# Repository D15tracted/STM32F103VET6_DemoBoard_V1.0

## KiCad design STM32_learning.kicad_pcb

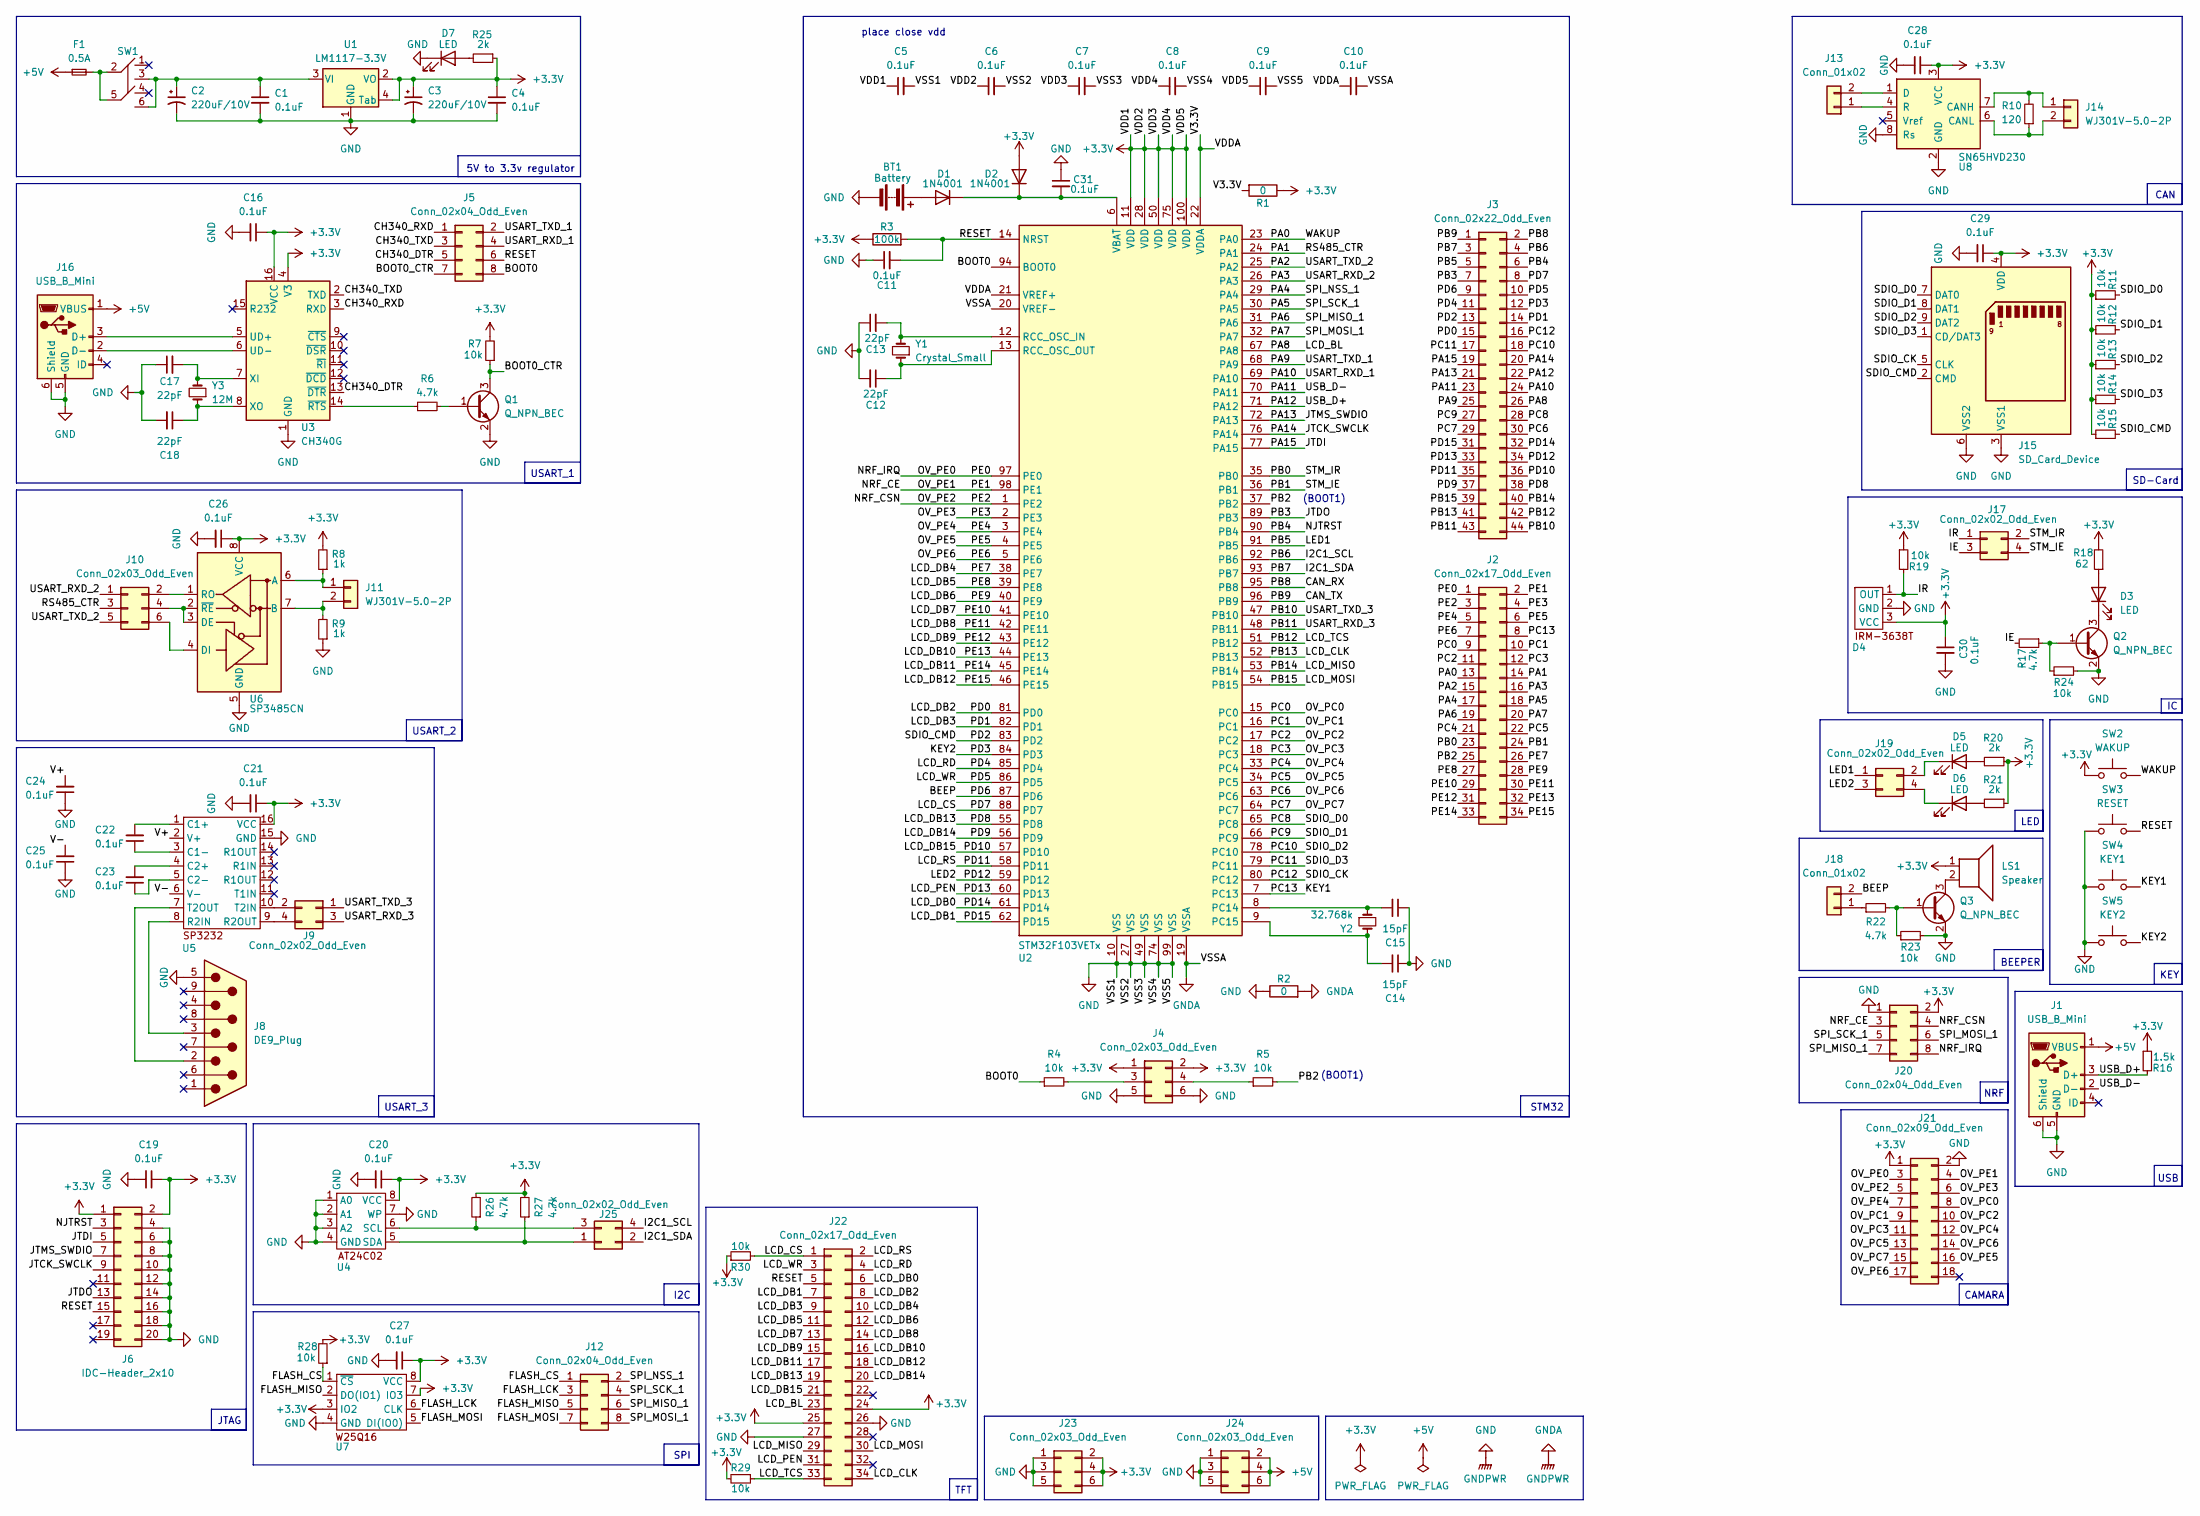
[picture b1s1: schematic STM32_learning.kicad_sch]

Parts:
BT1: Battery; CR1220-2
C1, C4, C5, C6, C7, C8, C9, C10, C11, C16, C19, C20, C21, C22, C23, C24, C25, C26, C27, C28, C29, C30, C31: 0.1uF; C_0603_1608Metric
C2, C3: 220uF/10V; C_Elec_6.3x5.4
C12, C13, C17, C18: 22pF; C_0603_1608Metric
C14, C15: 15pF; C_0603_1608Metric
D1, D2: 1N4001; D_MiniMELF
D3: LED; LED_D5.0mm_Horizontal_O3.81mm_Z15.0mm
D4: IRM-3638T
D5, D6, D7: LED; LED_0805_2012Metric
F1: 0.5A; Fuse_0805_2012Metric
J1, J16: USB_B_Mini; USB_Mini-B_Wuerth_65100516121_Horizontal
J2: Conn_02x17_Odd_Even; Conn2x17P
J3: Conn_02x22_Odd_Even; Conn2x22P
J4, J10, J23, J24: Conn_02x03_Odd_Even; Conn2x03P
J5, J12, J20: Conn_02x04_Odd_Even; Conn2x04P
J6: IDC-Header_2x10; IDC-Header_2x10_P2.54mm_Vertical
J8: DE9_Plug; DSUB-9_Female_Horizontal_P2.77x2.84mm_EdgePinOffset4.94mm_H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
J9, J17, J19, J25: Conn_02x02_Odd_Even; Conn2x02P
J11, J14: WJ301V-5.0-2P
J13, J18: Conn_01x02; Conn1x02P
J15: SD_Card_Device; SD-102
J21: Conn_02x09_Odd_Even; Conn2x09P
J22: Conn_02x17_Odd_Even; SKUMRB2801
LS1: Speaker; Beeper9mm
Q1, Q2, Q3: Q_NPN_BEC; SOT-23
R1, R2: 0; R_0603_1608Metric
R3: 100k; R_0603_1608Metric
R4, R5, R7, R11, R12, R13, R14, R15, R19, R23, R24, R28, R29, R30: 10k; R_0603_1608Metric
R6, R17, R22, R26, R27: 4.7k; R_0603_1608Metric
R8, R9: 1k; R_0603_1608Metric
R10: 120; R_0603_1608Metric
R16: 1.5k; R_0603_1608Metric
R18: 62; R_0805_2012Metric
R20, R21, R25: 2k; R_0603_1608Metric
SW1: TK-6580-1
SW2: WAKUP; KEY6x6
SW3: RESET; KEY6x6
SW4: KEY1; KEY6x6
SW5: KEY2; KEY6x6
U1: LM1117-3.3V; SOT-223
U2: STM32F103VETx; LQFP-100_14x14mm_P0.5mm
U3: CH340G; SOIC-16_3.9x9.9mm_P1.27mm
U4, U7: SOIC-8
U5: SOIC-16
U6: SP3485CN; SOIC-8_3.9x4.9mm_P1.27mm
U8: SN65HVD230; SOIC-8_3.9x4.9mm_P1.27mm
Y1: Crystal_Small; Crystal_HC49-U_Vertical
Y2: 32.768k; SMD-3215-2P
Y3: 12M; Crystal_HC49-U_Vertical

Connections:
+3.3V: C3.1, C4.1, C5.1, C6.1, C7.1, C8.1, C9.1, C16.1, C19.1, C20.1, C21.1, C26.1, C27.1, C28.1, C29.1, C30.1, D2.2 (A), D4.3 (VCC), J4.1, J4.2, J6.1, J6.2, J15.4 (VDD), J20.2, J21.1, J22.24, J22.25, J23.2, J23.4, J23.6, LS1.1, R1.1, R3.1, R7.2, R8.2, R11.1, R12.1, R13.1, R14.1, R15.1, R16.1, R18.2, R19.1, R20.1, R21.1, R25.1, R26.2, R27.2, R28.2, R29.2, R30.1, SW2.1, U1.2 (VO), U1.4 (Tab), U2.11 (VDD), U2.28 (VDD), U2.50 (VDD), U2.75 (VDD), U2.100 (VDD), U3.4 (V3), U3.16 (VCC), U4.8 (VCC), U5.16 (VCC), U6.8 (VCC), U7.3 (IO2), U7.7 (IO3), U7.8 (VCC), U8.3 (VCC)
/BEEP: J3.9, J18.2, U2.87 (PD6)
/BOOT0: J5.8, R4.1, U2.94 (BOOT0)
/BOOT0_CTR: J5.7, Q1.3 (C), R7.1
/CAN_RX: J3.2, U2.95 (PB8)
/CAN_TX: J3.1, U2.96 (PB9)
/CH340_DTR: J5.5, U3.13 (~DTR)
/CH340_RXD: J5.1, U3.3 (RXD)
/CH340_TXD: J5.3, U3.2 (TXD)
/FLASH_CS: J12.1, R28.1, U7.1 (~CS)
/FLASH_LCK: J12.3, U7.6 (CLK)
/FLASH_MISO: J12.5, U7.2 (DO(IO1))
/FLASH_MOSI: J12.7, U7.5 (DI(IO0))
/I2C1_SCL: J3.4, J25.4, U2.92 (PB6)
/I2C1_SDA: J3.3, J25.2, U2.93 (PB7)
/IE: J17.3, R17.2
/IR: D4.1 (OUT), J17.1, R19.2
/JTCK_SWCLK: J3.20, J6.9, U2.76 (PA14)
/JTDI: J3.19, J6.5, U2.77 (PA15)
/JTDO: J3.7, J6.13, U2.89 (PB3)
/JTMS_SWDIO: J3.21, J6.7, U2.72 (PA13)
/KEY1: J2.8, SW4.2, U2.7 (PC13)
/KEY2: J3.12, SW5.2, U2.84 (PD3)
/LCD_BL: J3.26, J22.23, U2.67 (PA8)
/LCD_CLK: J3.41, J22.34, U2.52 (PB13)
/LCD_CS: J3.8, J22.1, R30.2, U2.88 (PD7)
/LCD_DB0: J3.32, J22.6, U2.61 (PD14)
/LCD_DB1: J3.31, J22.7, U2.62 (PD15)
/LCD_DB2: J3.15, J22.8, U2.81 (PD0)
/LCD_DB3: J3.14, J22.9, U2.82 (PD1)
/LCD_DB4: J2.26, J22.10, U2.38 (PE7)
/LCD_DB5: J2.27, J22.11, U2.39 (PE8)
/LCD_DB6: J2.28, J22.12, U2.40 (PE9)
/LCD_DB7: J2.29, J22.13, U2.41 (PE10)
/LCD_DB8: J2.30, J22.14, U2.42 (PE11)
/LCD_DB9: J2.31, J22.15, U2.43 (PE12)
/LCD_DB10: J2.32, J22.16, U2.44 (PE13)
/LCD_DB11: J2.33, J22.17, U2.45 (PE14)
/LCD_DB12: J2.34, J22.18, U2.46 (PE15)
/LCD_DB13: J3.38, J22.19, U2.55 (PD8)
/LCD_DB14: J3.37, J22.20, U2.56 (PD9)
/LCD_DB15: J3.36, J22.21, U2.57 (PD10)
/LCD_MISO: J3.40, J22.29, U2.53 (PB14)
/LCD_MOSI: J3.39, J22.30, U2.54 (PB15)
/LCD_PEN: J3.33, J22.31, U2.60 (PD13)
/LCD_RD: J3.11, J22.4, U2.85 (PD4)
/LCD_RS: J3.35, J22.2, U2.58 (PD11)
/LCD_TCS: J3.42, J22.33, R29.1, U2.51 (PB12)
/LCD_WR: J3.10, J22.3, U2.86 (PD5)
/LED1: J3.5, J19.1, U2.91 (PB5)
/LED2: J3.34, J19.3, U2.59 (PD12)
/NJTRST: J3.6, J6.3, U2.90 (PB4)
/NRF_CE: J2.2, J20.3, J21.4, U2.98 (PE1)
/NRF_CSN: J2.3, J20.4, J21.5, U2.1 (PE2)
/NRF_IRQ: J2.1, J20.8, J21.3, U2.97 (PE0)
/OV_PC0: J2.9, J21.8, U2.15 (PC0)
/OV_PC1: J2.10, J21.9, U2.16 (PC1)
/OV_PC2: J2.11, J21.10, U2.17 (PC2)
/OV_PC3: J2.12, J21.11, U2.18 (PC3)
/OV_PC4: J2.21, J21.12, U2.33 (PC4)
/OV_PC5: J2.22, J21.13, U2.34 (PC5)
/OV_PC6: J3.30, J21.14, U2.63 (PC6)
/OV_PC7: J3.29, J21.15, U2.64 (PC7)
/OV_PE3: J2.4, J21.6, U2.2 (PE3)
/OV_PE4: J2.5, J21.7, U2.3 (PE4)
/OV_PE5: J2.6, J21.16, U2.4 (PE5)
/OV_PE6: J2.7, J21.17, U2.5 (PE6)
/PA0: J2.13, SW2.2, U2.23 (PA0)
/PA1: J2.14, J10.3, U2.24 (PA1)
/PA2: J2.15, J10.5, U2.25 (PA2)
/PA3: J2.16, J10.1, U2.26 (PA3)
/PA4: J2.17, J12.2, U2.29 (PA4)
/PA5: J2.18, J12.4, J20.5, U2.30 (PA5)
/PA6: J2.19, J12.6, J20.7, U2.31 (PA6)
/PA7: J2.20, J12.8, J20.6, U2.32 (PA7)
/PA9: J3.25, J5.2, U2.68 (PA9)
/PA10: J3.24, J5.4, U2.69 (PA10)
/PA11: J1.2 (D-), J3.23, U2.70 (PA11)
/PA12: J1.3 (D+), J3.22, R16.2, U2.71 (PA12)
/PB0: J2.23, J17.2, U2.35 (PB0)
/PB1: J2.24, J17.4, U2.36 (PB1)
/PB2: J2.25, R5.2, U2.37 (PB2)
/PB10: J3.44, J9.1, U2.47 (PB10)
/PB11: J3.43, J9.3, U2.48 (PB11)
/PC8: J3.28, J15.7 (DAT0), R11.2, U2.65 (PC8)
/PC9: J3.27, J15.8 (DAT1), R12.2, U2.66 (PC9)
/PC10: J3.18, J15.9 (DAT2), R13.2, U2.78 (PC10)
/PC11: J3.17, J15.1 (CD/DAT3), R14.2, U2.79 (PC11)
/PC12: J3.16, J15.5 (CLK), U2.80 (PC12)
/PD2: J3.13, J15.2 (CMD), R15.2, U2.83 (PD2)
/RESET: C11.2, J5.6, J6.15, J22.5, R3.2, SW3.2, U2.14 (NRST)
/V3.3V: C10.1, R1.2, U2.21 (VREF+), U2.22 (VDDA)
/V+: C24.2, U5.2 (V+)
/V-: C25.2, U5.6 (V-)
GND: BT1.2 (-), C1.2, C2.2, C3.2, C4.2, C5.2, C6.2, C7.2, C8.2, C9.2, C10.2, C11.1, C12.2, C13.1, C14.1, C15.1, C16.2, C17.1, C18.2, C19.2, C20.2, C21.2, C24.1, C25.1, C26.2, C27.2, C28.2, C29.2, C30.2, C31.1, D4.2 (GND), D7.1 (K), J1.5 (GND), J1.6 (Shield), J4.5, J4.6, J6.4, J6.6, J6.8, J6.10, J6.12, J6.14, J6.16, J6.18, J6.20, J8.5, J15.3 (VSS1), J15.6 (VSS2), J16.5 (GND), J16.6 (Shield), J20.1, J21.2, J22.26, J22.27, J23.1, J23.3, J23.5, J24.1, J24.3, J24.5, Q1.2 (E), Q2.2 (E), Q3.2 (E), R2.1, R2.2, R9.1, R23.2, R24.2, SW3.1, SW4.1, SW5.1, U1.1 (GND), U2.10 (VSS), U2.19 (VSSA), U2.20 (VREF-), U2.27 (VSS), U2.49 (VSS), U2.74 (VSS), U2.99 (VSS), U3.1 (GND), U4.1 (A0), U4.2 (A1), U4.3 (A2), U4.4 (GND), U4.7 (WP), U5.15 (GND), U6.5 (GND), U7.4 (GND), U8.2 (GND), U8.8 (Rs)
unnamed: BT1.1 (+), D1.2 (A)
unnamed: C31.2, D1.1 (K), D2.1 (K), U2.6 (VBAT)
unnamed: D3.2 (A), R18.1
unnamed: D3.1 (K), Q2.3 (C)
unnamed: D5.2 (A), R20.2
unnamed: D5.1 (K), J19.2
unnamed: D6.2 (A), R21.2
unnamed: D6.1 (K), J19.4
unnamed: D7.2 (A), R25.2
unnamed: F1.2, SW1.2, SW1.5
unnamed: J4.3, R4.2
unnamed: J4.4, R5.1
unnamed: J9.2, U5.10 (T2IN)
unnamed: J9.4, U5.9 (R2OUT)
unnamed: J10.2, U6.1 (RO)
unnamed: J10.4, U6.2 (~RE), U6.3 (DE)
unnamed: J10.6, U6.4 (DI)
unnamed: J11.1, R8.1, U6.6 (A)
unnamed: J11.2, R9.2, U6.7 (B)
unnamed: J13.1, U8.4 (R)
unnamed: J13.2, U8.1 (D)
unnamed: J14.1, R10.2, U8.7 (CANH)
unnamed: J14.2, R10.1, U8.6 (CANL)
unnamed: J16.3 (D+), U3.5 (UD+)
unnamed: J16.2 (D-), U3.6 (UD-)
unnamed: J18.1, R22.1
unnamed: J25.1, R27.1, U4.5 (SDA)
unnamed: J25.3, R26.1, U4.6 (SCL)
unnamed: Q1.1 (B), R6.2
unnamed: Q2.1 (B), R17.1, R24.1
unnamed: Q3.1 (B), R22.2, R23.1
unnamed: LS1.2, Q3.3 (C)
unnamed: C15.2, U2.8 (PC14), Y2.1
unnamed: C14.2, U2.9 (PC15), Y2.2
unnamed: C13.2, U2.12 (RCC_OSC_IN), Y1.2
unnamed: C12.1, U2.13 (RCC_OSC_OUT), Y1.1
unnamed: C17.2, U3.7 (XI), Y3.2
unnamed: C18.1, U3.8 (XO), Y3.1
unnamed: R6.1, U3.14 (~RTS)
unnamed: C22.2, U5.1 (C1+)
unnamed: C22.1, U5.3 (C1-)
unnamed: C23.2, U5.4 (C2+)
unnamed: C23.1, U5.5 (C2-)
unnamed: J8.3, U5.8 (R2IN)
unnamed: J8.2, U5.7 (T2OUT)

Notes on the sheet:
CAN
USART_2
KEY
BEEPER
STM32
I2C
LED
5V to 3.3v regulator
USB
CAMARA
TFT
JTAG
SPI
NRF
USART_1
place close vdd
USART_3
(BOOT1)
SD-Card

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
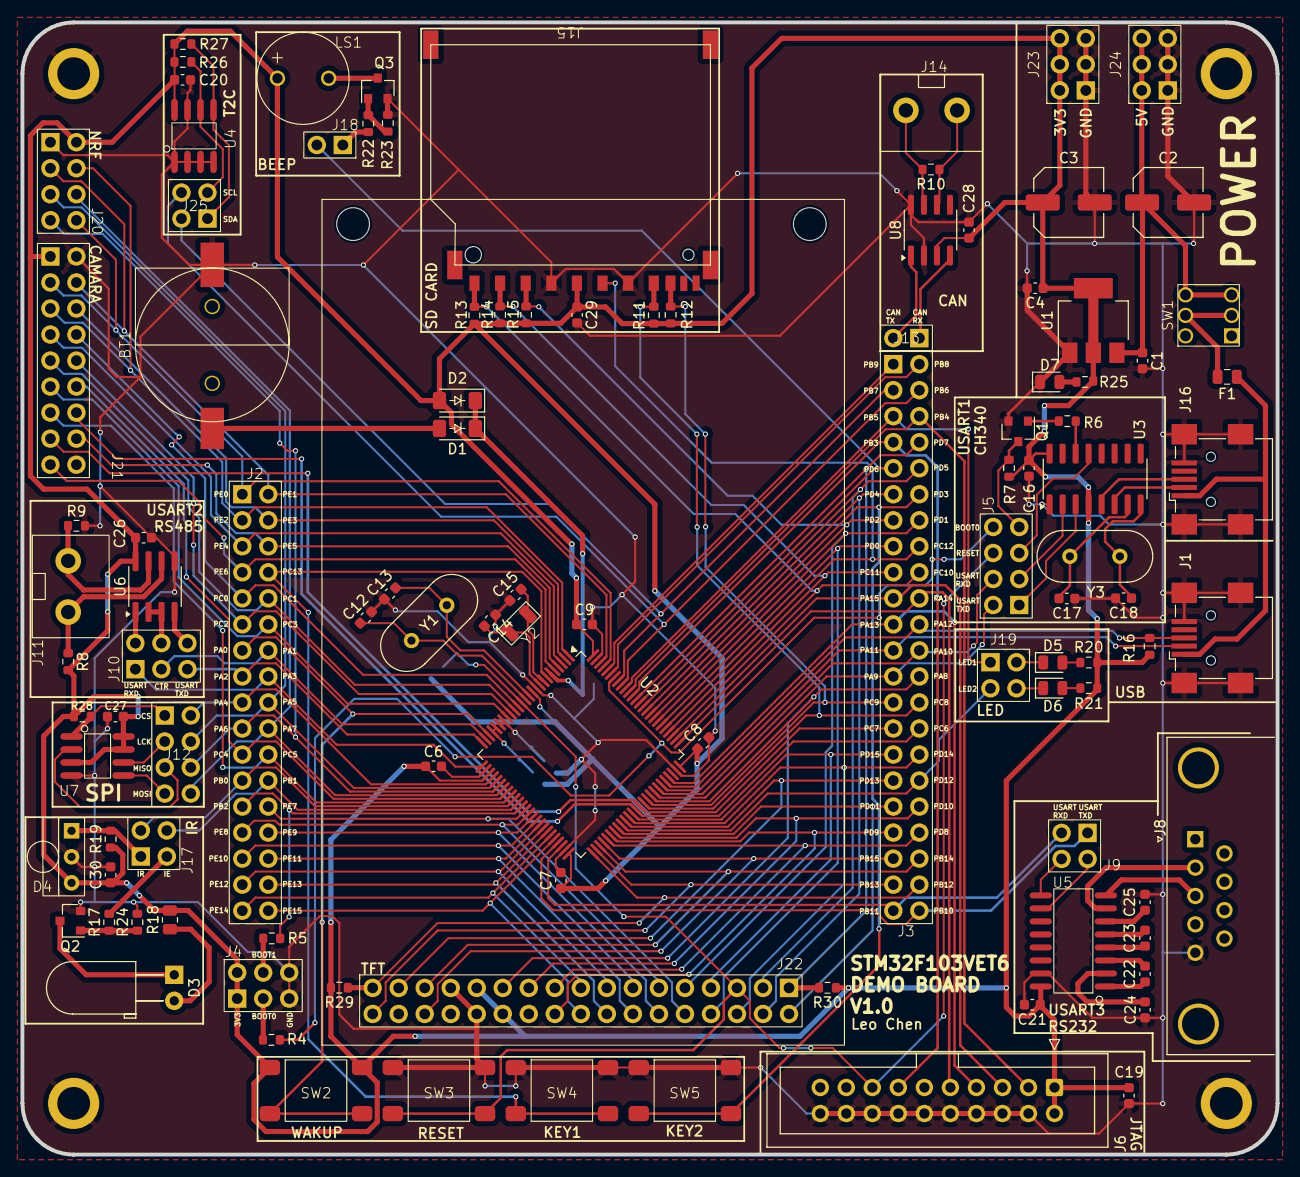
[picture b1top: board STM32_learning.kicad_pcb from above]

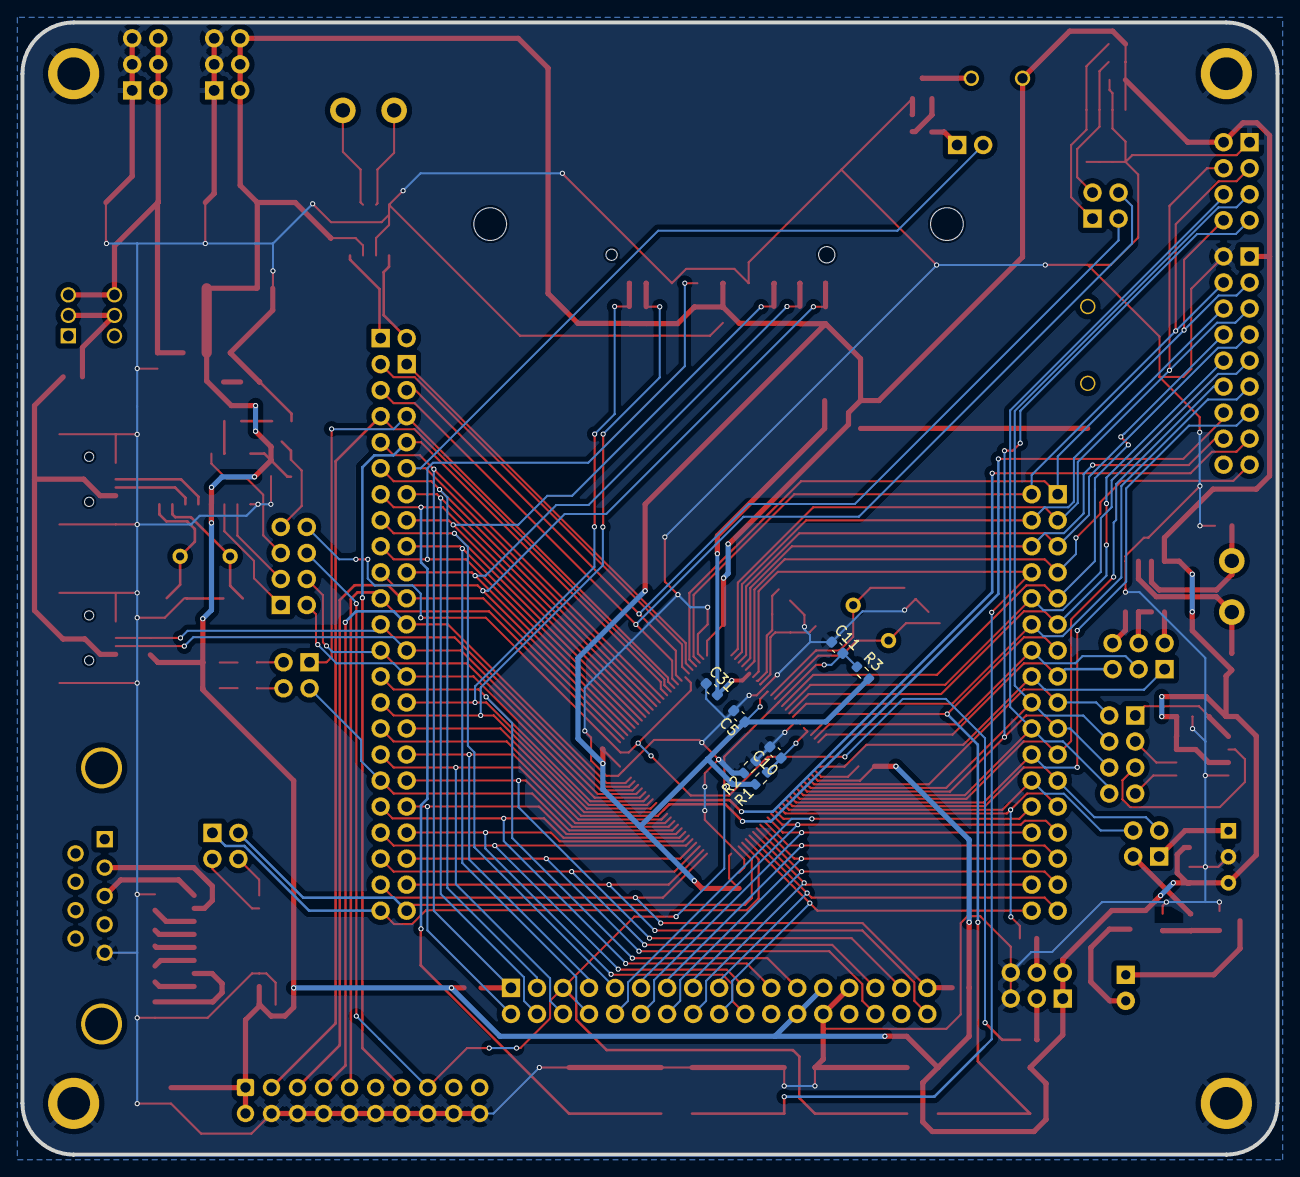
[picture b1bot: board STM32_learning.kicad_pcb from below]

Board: 2 copper layers, 122.5 x 110.5 mm, 114 parts (7 on the bottom side), 142 nets.

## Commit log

2026-02-21 初始提交
